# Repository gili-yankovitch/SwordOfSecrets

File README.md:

# Sword of Secrets
Unlock the hidden secrets of the sword. What kind of secrets lie in waiting? Designed for security researchers and hardware enthusiasts, the Sword of Secrets is your ultimate mystery in digital exploration.

### About The Project
Sword of Secrets is a hardware hacking challenge. It is suitable for both novice and experienced tinkerers and hackers. It utilizes a low number of components to make the challenge easier to grasp, but hold in itself enough intricacies that will require the challenger a keen eye and sharp mind to solve all challenges.

To solve the challenge you will need to discover a series of flags, hidden inside the sword. Each one will help you unlock the next step in the challenge, to finally reveal the ultimate secret the sword holds.

## How to Solve
You, as the challenger, will face  a couple of tricks on the hardware level. It is strongly recomended to identify which chips are used, find their datasheet and understand how they are connected. Then, dive into the software to understand how it is built and figure out what needs to be done to make the sword uncover its truth to you. All the software (except the encryption keys and the flags) is available here on this repository. It is recommended to try and reverse engineer the PCB before heading towards the `hw` folder.

### Source structure
* `aes.cpp` [AES implementation](https://github.com/kokke/tiny-AES-c)
* `main.cpp` Boot and Setup

... The rest is up to you. :-)

### You Will Need
The following list is a recommended list of equipment that is suggested to solve the challenge:
* Multimeter
* Soldering Iron
* Jumper wires
* An external microcontroller (Any Arduino/RPi)

### Software
Please install the following software to be able to flash software to the device:
* [ch32fun](https://github.com/cnlohr/ch32fun/wiki/Installation) Follow install guide for toolchain and `minichlink` flash utility
* [Flash Update](https://swordofsecrets.com/update.html) Use online update tool to update the sword using preflashed bootloader

### Hardware
All PCB specs are provided here under `hw/`. This can be easily manufactured as well as paneled for a larger volume. There are no special requirements for this board's manufacturing process.

#### Bill of Materials
| Quantity | Component Description | Datasheet |
|----------|-----------------------|-----------|
| 1 | CH32V003 RISC-V Microcontroller | [Datasheet](http://mcu.cz/images_articles/5007-CH32V003Reference-Manual.PDF) |
| 1 | AMS1117-3.3 LDO Voltage Regulator | [Datasheet](https://www.ti.com/lit/gpn/lm1117) |
| 1 | CH340N USB-toSerial | [Datasheet](https://cdn.sparkfun.com/assets/5/0/a/8/5/CH340DS1.PDF) |
| 1 | W25Q128JVSIQ 128MB NOR Flash | [Datasheet](https://www.mouser.co.il/datasheet/2/949/w25q128jv_revf_03272018_plus-1489608.pdf) |
| 1 | SMD 10 kOhms 0805 Resistor|  |
| 1 | SMD 100 kOhms 0805 Resistor |  |
| 3 | SMD 0.1 uF 0805 Capacitor |  |

<!-- LICENSE -->
## License

Distributed under the MIT License.

<p align="right">(<a href="#readme-top">back to top</a>)</p>

<!-- CONTACT -->
## Contact

Gili Yankovitch - [@GiliYankovitch](https://x.com/GiliYankovitch) - giliy@nyxsecurity.net

Project Link: [https://gili-yankovitch.github.io/SwordOfSecrets](https://gili-yankovitch.github.io/SwordOfSecrets)

<!-- MARKDOWN LINKS & IMAGES -->
<!-- https://www.markdownguide.org/basic-syntax/#reference-style-links -->
[front]: images/front.png
[back]: images/back.png

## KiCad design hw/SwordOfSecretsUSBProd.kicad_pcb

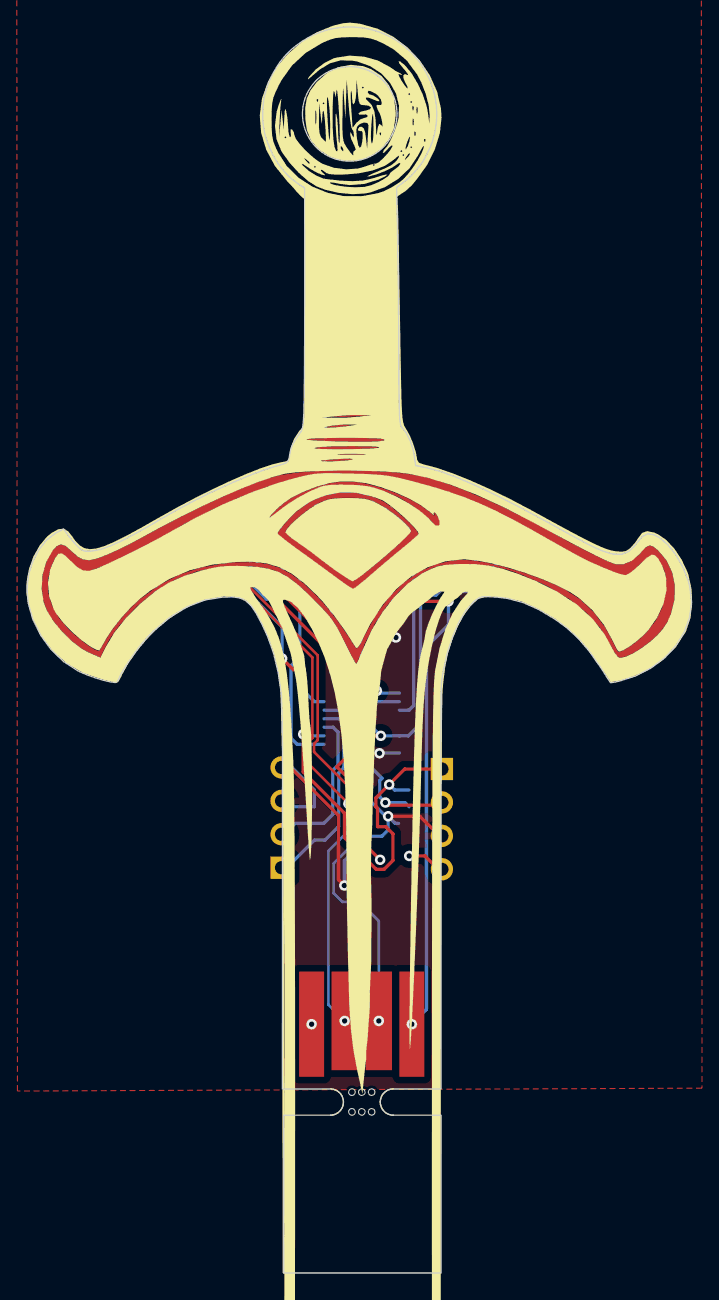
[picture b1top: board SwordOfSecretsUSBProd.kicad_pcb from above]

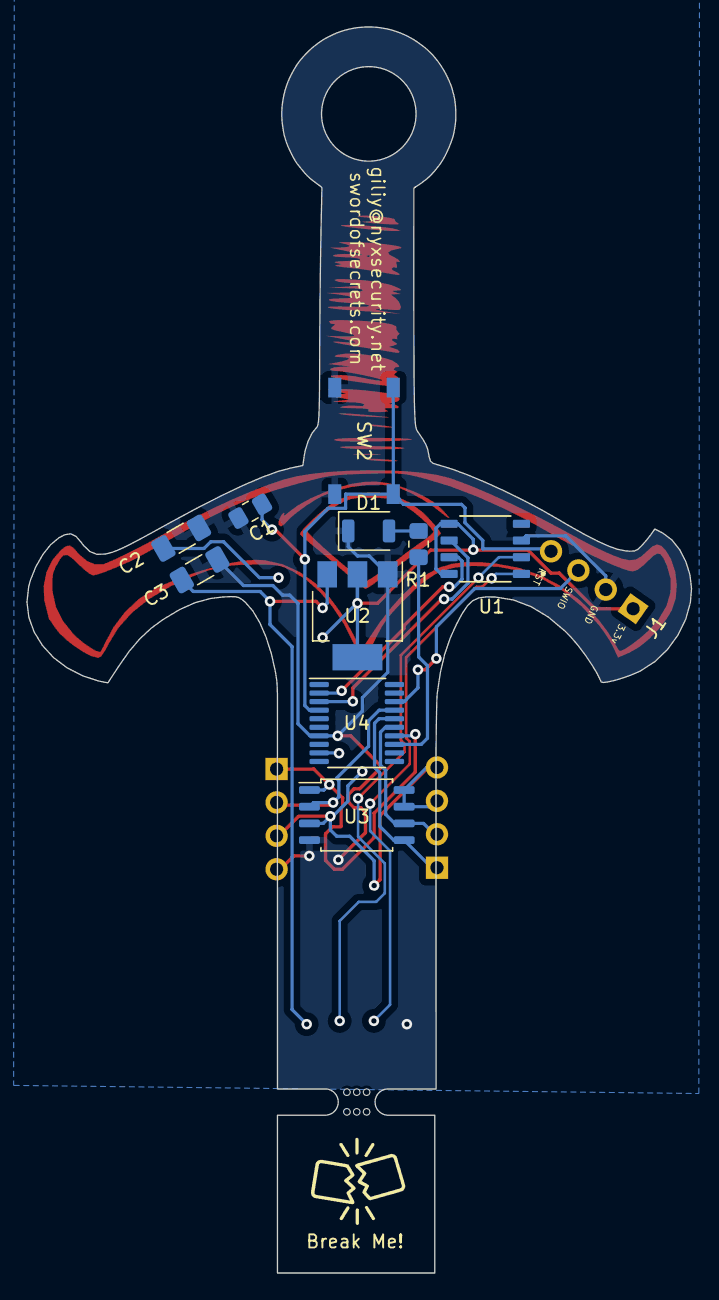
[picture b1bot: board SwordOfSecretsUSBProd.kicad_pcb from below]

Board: 2 copper layers, 50.5 x 94.7 mm, 14 parts (10 on the bottom side), 15 nets.

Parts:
C1: 0.1uF; C_0805_2012Metric_Pad1.18x1.45mm_HandSolder
C2, C3: 0.1uF; C_1206_3216Metric_Pad1.33x1.80mm_HandSolder
D1: LED; LED_1206_3216Metric_ReverseMount_Hole1.8x2.4mm
J1, J3, J4: Conn_01x04_Pin; PinHeader_1x04_P2.54mm_Vertical
J2: USB_A; usb-PCB
R1: 100; R_0805_2012Metric_Pad1.20x1.40mm_HandSolder
SW2: SW_Push; SMD-BTN-6x6-4Pin
U1: CH340N; SOIC127P600X160-8N
U2: AMS1117-3.3; SOT-223-3_TabPin2
U3: W25Q128JVS; SOIC-8_5.23x5.23mm_P1.27mm
U4: CH32V003F4P6; TSSOP-20_4.4x6.5mm_P0.65mm

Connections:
3.3v: C2.2, J1.1, J3.3, J4.3, J4.4, U1.5 (VCC), U1.8 (V3), U2.2 (VO), U3.3 (IO2), U3.7 (IO3), U3.8 (VCC), U4.9 (VDD)
D+: J2.3 (D+), U1.1 (UD+)
D-: J2.2 (D-), U1.2 (UD-)
GND: C1.2, C2.1, C3.2, D1.1 (K), J1.2, J2.4 (GND), J3.4, SW2.1, U1.3 (GND), U2.1 (GND), U3.4 (GND), U4.7 (VSS)
MISO: J3.2, U3.2 (DO(IO1)), U4.17 (PC7)
MOSI: J4.1, U3.5 (DI(IO0)), U4.16 (PC6)
unnamed: D1.2 (A), R1.2
PC3: R1.1, U4.13 (PC3)
PC4: J3.1, U3.1 (~CS), U4.14 (PC4)
RST: C1.1, J1.4, SW2.2, U4.4 (NRST/PD7)
RX: U1.6 (TXD), U4.3 (PD6)
RXOUT: U1.7 (RXD), U4.2 (PD5)
SCK: J4.2, U3.6 (CLK), U4.15 (PC5)
SWIO: J1.3, U4.18 (PD1)
VCC: C3.1, J2.1 (VBUS), U2.3 (VI)

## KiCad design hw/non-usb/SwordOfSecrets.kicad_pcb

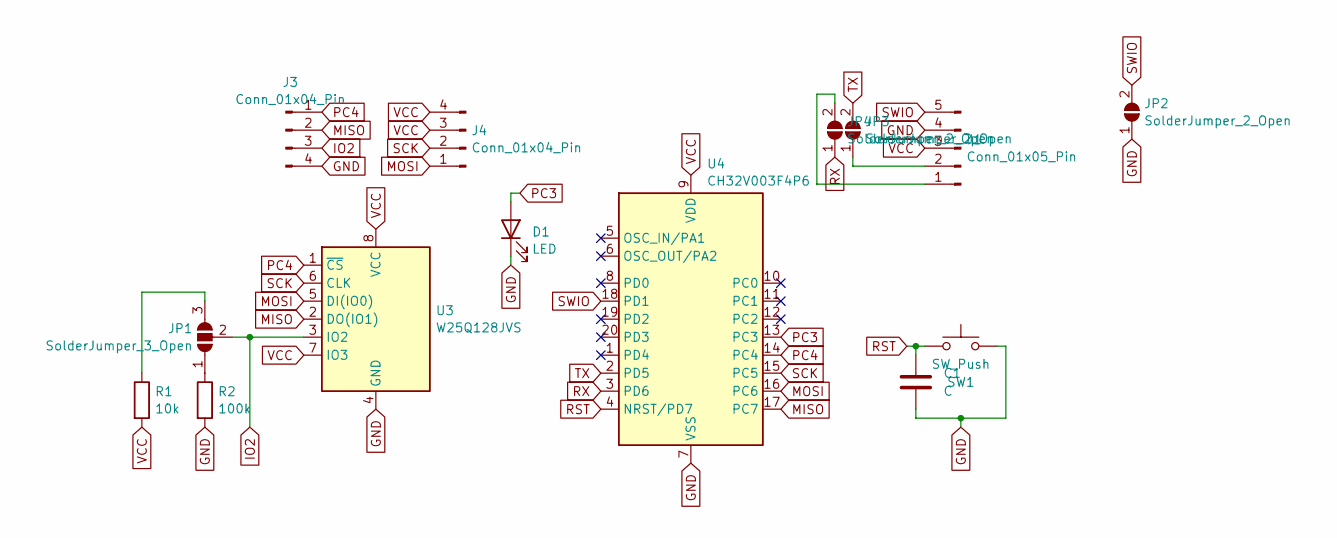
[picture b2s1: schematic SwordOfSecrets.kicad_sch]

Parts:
C1: C; C_0805_2012Metric_Pad1.18x1.45mm_HandSolder
D1: LED; LED_0805_2012Metric_Pad1.15x1.40mm_HandSolder
J1: Conn_01x05_Pin; PinHeader_1x05_P2.54mm_Vertical
J3, J4: Conn_01x04_Pin; PinHeader_1x04_P2.54mm_Vertical
JP1: SolderJumper_3_Open; SolderJumper-3_P1.3mm_Open_RoundedPad1.0x1.5mm
JP2, JP3, JP4: SolderJumper_2_Open; SolderJumper-2_P1.3mm_Open_Pad1.0x1.5mm
R1: 10k; R_0805_2012Metric_Pad1.20x1.40mm_HandSolder
R2: 100k; R_0805_2012Metric_Pad1.20x1.40mm_HandSolder
SW1: SW_Push; SMD-BTN-6x6-4Pin
U3: W25Q128JVS; SOIC-8_5.23x5.23mm_P1.27mm
U4: CH32V003F4P6; TSSOP-20_4.4x6.5mm_P0.65mm

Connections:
GND: C1.2, D1.1 (K), J1.4, J3.4, JP2.1 (A), R2.2, U3.4 (GND), U4.7 (VSS); also elsewhere on the board
IO2: J3.3, JP1.2 (C), U3.3 (IO2)
MISO: J3.2, U3.2 (DO(IO1)), U4.17 (PC7)
MOSI: J4.1, U3.5 (DI(IO0)), U4.16 (PC6)
unnamed: J1.1, JP4.2 (B)
unnamed: J1.2, JP3.1 (A)
unnamed: JP1.1 (A), R2.1
unnamed: JP1.3 (B), R1.1
PC3: D1.2 (A), U4.13 (PC3)
PC4: J3.1, U3.1 (~CS), U4.14 (PC4)
RST: C1.1, U4.4 (NRST/PD7); also elsewhere on the board
RX: JP4.1 (A), U4.3 (PD6)
SCK: J4.2, U3.6 (CLK), U4.15 (PC5)
SWIO: J1.5, JP2.2 (B), U4.18 (PD1)
TX: JP3.2 (B), U4.2 (PD5)
VCC: J1.3, J4.3, J4.4, R1.2, U3.7 (IO3), U3.8 (VCC), U4.9 (VDD)

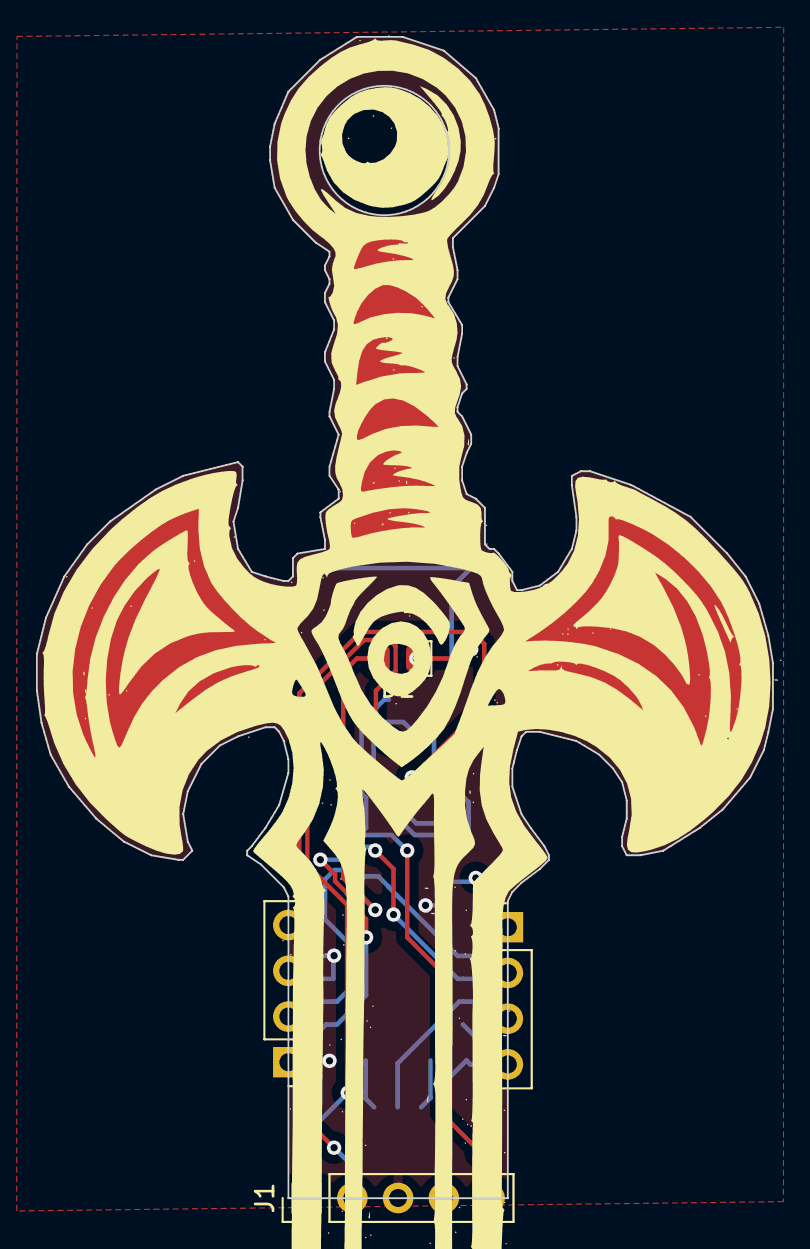
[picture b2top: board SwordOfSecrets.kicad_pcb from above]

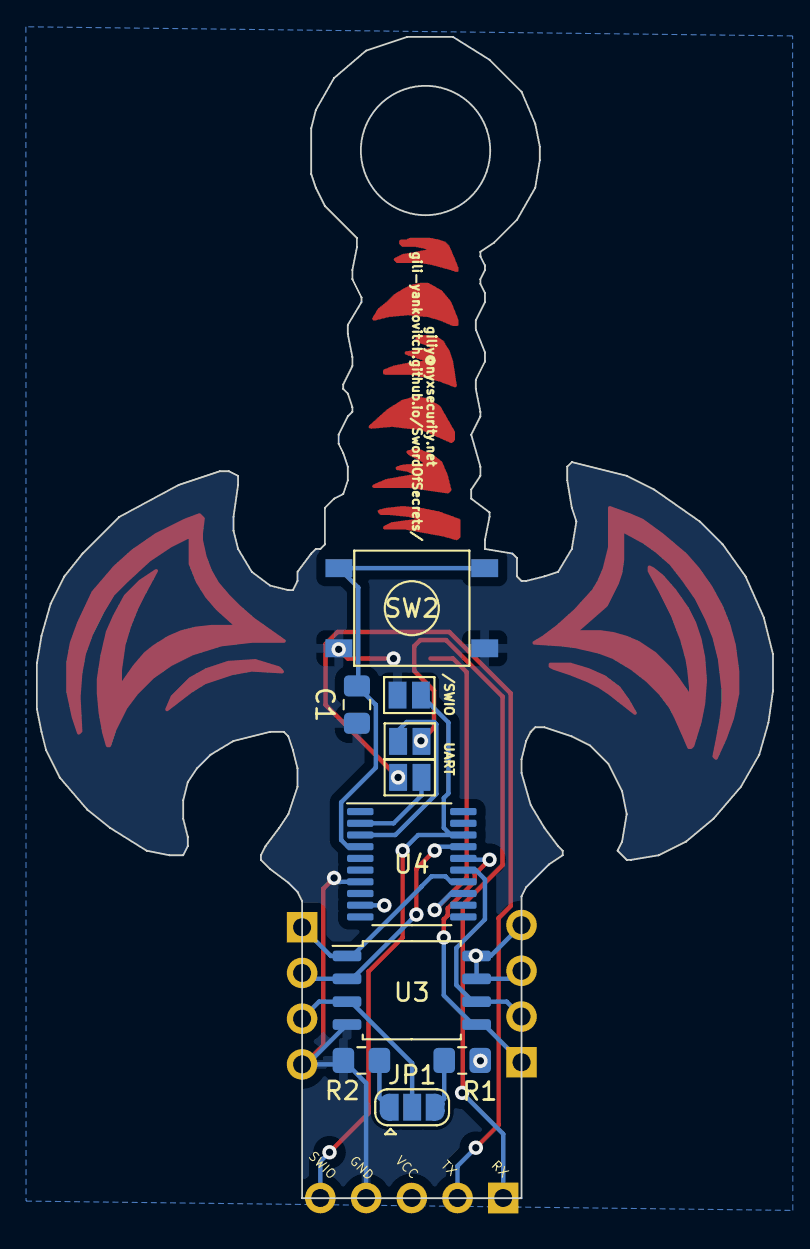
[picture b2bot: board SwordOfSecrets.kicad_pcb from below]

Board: 2 copper layers, 40.9 x 64.5 mm, 14 parts (10 on the bottom side), 16 nets.

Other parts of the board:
SW2: SW_Push; SMD-BTN-6x6-4Pin

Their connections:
GND: SW2.1; also elsewhere on the board
RST: SW2.2; also elsewhere on the board

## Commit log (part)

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2024-11-11 Handling a more sane internal flash utilization and cleaning code
2024-11-11 Adding hardware files and readme
2024-11-17 Adding the final stage
2024-11-18 Reshaping final stage
2024-11-18 Organizing code content
2024-11-18 Adding banner
2024-11-19 Fixing index page for mobile
2024-11-22 Fixing mobile title and adding sword to homepage
2024-11-22 Resizing sword
2024-11-23 Fixing sword image
2024-12-02 Adding the virtual challenge
2024-12-02 Fixing button spacing
2024-12-02 Fixing mobile styles
2024-12-02 Fixing emulator style
2024-12-02 Fixing styles
2024-12-04 Version update
2025-03-04 Adding PDF schematics
2025-03-04 Adding production version based on ch32v003fun instead of arduino
2025-04-03 Create CNAME
2025-04-12 Adding OTA update webpage
2025-04-12 Fixing typo
2025-04-12 Adding OTA subsystem to repo
2025-04-12 Updating README
2025-04-12 Adding the LICENSE according to used software packages
2025-05-04 Fixing interrupt vector placement inside bootloader
2025-05-22 Adding a CLI interface to allow solving the chellenge from the UART interface without using external HW
2025-05-23 Adding a riddle reset command
2025-05-26 Freeing bootloader section code size
2025-06-18 Updating WASM code to have a teaser stage
2025-07-01 Updating to the new Sword of Secrets look
2025-07-01 Resizing the sword on the website
2025-08-14 Uploading finalized hardware + Fixing emulator to work with SERIAL input to match the latest riddles
2025-08-25 Fixing main page on macos edge browser
2025-08-26 Adding the golden challenge
2025-11-07 chore: Adding missing files so repo compiles cleanly with fake keys
2025-11-08 Adding flashing + self-test script
2025-11-08 Adding printouts and tools printing labels
2025-11-22 chore: Fixing ota tool
2025-11-25 chore: Adding a reboot command and rebooting on flash init failure
2025-12-03 feat: Adding a 'getting-started' page to the website
2025-12-03 feat: Adding a firmware updates page
2025-12-03 chore: Fixing typo
2025-12-03 chore: Updating firmware file to download
2025-12-03 chore: Fixing github download URL
2025-12-03 chore: Reverting to relative paths for firmware files
2025-12-03 chore: Adding a 'Firmware Upgrade Utility' button in the firmware download webpage
2025-12-03 chore: Fixing instructions in various pages
2025-12-30 chore: Adding CrowdSupply link in main page
2026-03-05 chore: Updating schematics to reflect production PCB
2026-03-05 chore: Uploading a fancier version of kicad schematics file
2026-03-14 Multiple small updates:
    * Format makefile for easier review
    * Avoid variable in single-parameter printf()
    * Fix typo `GOLD_CHELLANGE` --> `GOLD_CHALLENGE` in secret.c
    * secret.c -- better BF script output
    * Remove unused files
    * update .gitignore
2026-03-14 Avoid accessing data beyond end of valid buffer
2026-03-14 Fix two more variable single-param printf
2026-03-14 remove duplicate `$(TARGET).hex`
2026-03-14 remove non-existent target from .PHONY
2026-03-14 fix to ensure null-terminated string
2026-03-14 Restore default make target to `all`
